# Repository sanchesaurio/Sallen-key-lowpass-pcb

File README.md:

# Sallen-Key Butterworth Low-Pass Filter — PCB Design and Fabrication

<p align="center">
  
  &nbsp;
  
</p>

University project for the course **Circuits i Tecnologies Electròniques** (Computer Engineering and Telecommunication Electronics). It covers the full life cycle of an electronic prototype: theoretical design, schematic and layout in Autodesk Eagle, board fabrication, soldering and experimental verification in the lab.

## Specifications

| Parameter | Value |
|---|---|
| Type | Active low-pass, Butterworth, 2nd order |
| Topology | Sallen-Key with an LF411N op-amp |
| Cutoff frequency (design) | 500 Hz |
| Cutoff frequency (measured) | **≈ 410 Hz** |
| Passband gain | 10 (20 dB) |
| Quality factor | Q = 1/√2 |
| Roll-off | −40 dB/decade |
| Board size | 55 × 35 mm, single-sided (Bottom) |

## Schematic and layout

The cutoff frequency is given by

$$f_c = \frac{1}{2\pi\sqrt{R_A R_B C_1 C_2}}$$

with R<sub>A</sub> = 63 kΩ (built as 50 kΩ + 13 kΩ in series, based on what was available in the lab), R<sub>B</sub> = 27 kΩ, C<sub>1</sub> = 2.7 nF and C<sub>2</sub> = 22 nF, giving a theoretical 500.7 Hz. The gain is set by the negative feedback network, with 1 kΩ to ground and 9 kΩ.

Design rules: minimum trace width 0.508 mm, clearance 0.58 mm, routed on the Bottom layer with 45° bends.

### Custom part: Vishay TSM4 potentiometer

The standard Eagle libraries did not include the SMD potentiometer we wanted to use, so we modeled it from scratch (symbol, footprint based on the datasheet, and device). It is in [`hardware/POTENCIOMETRO.lbr`](hardware/POTENCIOMETRO.lbr).

<p align="center">
  
  &nbsp;&nbsp;
  
</p>

In the final assembly it was replaced with a fixed 9 kΩ resistor to simplify the circuit.

## Bill of materials

| Ref. | Value | Package |
|---|---|---|
| IC1 | LF411N | DIP-8 |
| R1.1, R1.2 | 50 kΩ + 13 kΩ | THT 0207 |
| R2 | 27 kΩ | THT 0207 |
| R5 | 1 kΩ | THT 0207 |
| 9K | 9 kΩ (TSM4 potentiometer in the design) | SMD TSM4 |
| C1 | 2.7 nF | THT, 5 mm pitch |
| C2 | 22 nF | THT, 5 mm pitch |
| X1, X2 | BNC coaxial connector (input/output) | AMP 227161 |
| X3 | 3-way terminal block (±V, GND) | AK500/3 |
| SJ1, SJ2, SJ6 | Solder jumpers | SJW |

## Fabrication

The final board was made by **mechanical milling** on an LPKF ProtoMat H100. We also tried and compared two other methods: 3D printing with silver ink (Voltera V-One) and chemical etching (photolithography). We also characterized the parasitics of the FR4 board (for example, about 346 pF of capacitance on a blank 7.4 × 10 cm board).

<p align="center">
  
  &nbsp;
  
</p>

## Results

We swept from 10 Hz to 10 kHz with a 1 V peak sine wave and measured the output on the oscilloscope.

- The gain stays flat at 20 dB at low frequencies.
- The actual cutoff frequency (−3 dB) is around **410 Hz**, 18% below the design value. This is attributed to component tolerances (1–5% for resistors, 10% for capacitors) and to parasitic capacitance on the PCB.
- From about 700 Hz, the attenuation reaches the −40 dB/decade expected from a 2nd-order filter.

## Repository structure

```
├── hardware/
│   ├── CiTEsch2.sch         # Schematic (Eagle 9.6.2)
│   ├── CiTEsch2.brd         # PCB layout
│   └── POTENCIOMETRO.lbr    # TSM4 potentiometer library
└── docs/
    └── img/                 # Images used in this README
```

The `.sch` and `.brd` files open in Autodesk Eagle or Fusion (Electronics). They can also be imported into **KiCad** (free): *File → Import → Non-KiCad Project → Eagle*.

## Authors

- Guillem Simon Rodriguez
- Oriol Sanchez Romero

May 2026.

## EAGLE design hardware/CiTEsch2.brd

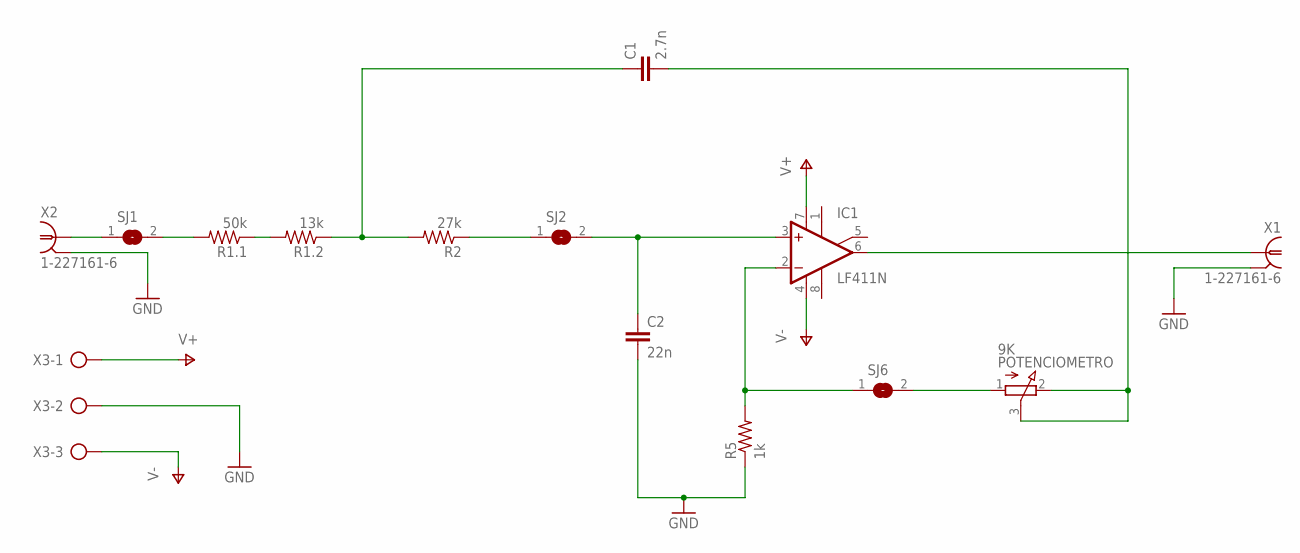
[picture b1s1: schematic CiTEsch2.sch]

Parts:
9K: POTENCIOMETRO; TSM4YJ
C1: 2.7n; C050-025X075
C2: 22n; C050-025X075
IC1: LF411N; DIL08
R1.1: 50k; 0207/10
R1.2: 13k; 0207/10
R2: 27k; 0207/10
R5: 1k; 0207/10
SJ1, SJ2, SJ6: SJW
X1, X2: 1-227161-6; AMP_227161
X3: AK500/3

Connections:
GND: C2.2, R5.1, X1.2, X2.2, X3.2
unnamed: SJ1.1, X2.1
unnamed: R1.1.2, SJ1.2
unnamed: 9K.2 (E), 9K.3 (S), C1.2, IC1.6 (OUT), X1.1
unnamed: R1.1.1, R1.2.2
unnamed: C1.1, R1.2.1, R2.2
unnamed: 9K.1 (A), SJ6.2
unnamed: IC1.2 (-IN), R5.2, SJ6.1
unnamed: R2.1, SJ2.1
unnamed: C2.1, IC1.3 (+IN), SJ2.2
V+: IC1.7 (V+), X3.1
V-: IC1.4 (V-), X3.3

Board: 2 copper layers, 14 parts (0 on the bottom side), 12 nets, no tracks yet.
